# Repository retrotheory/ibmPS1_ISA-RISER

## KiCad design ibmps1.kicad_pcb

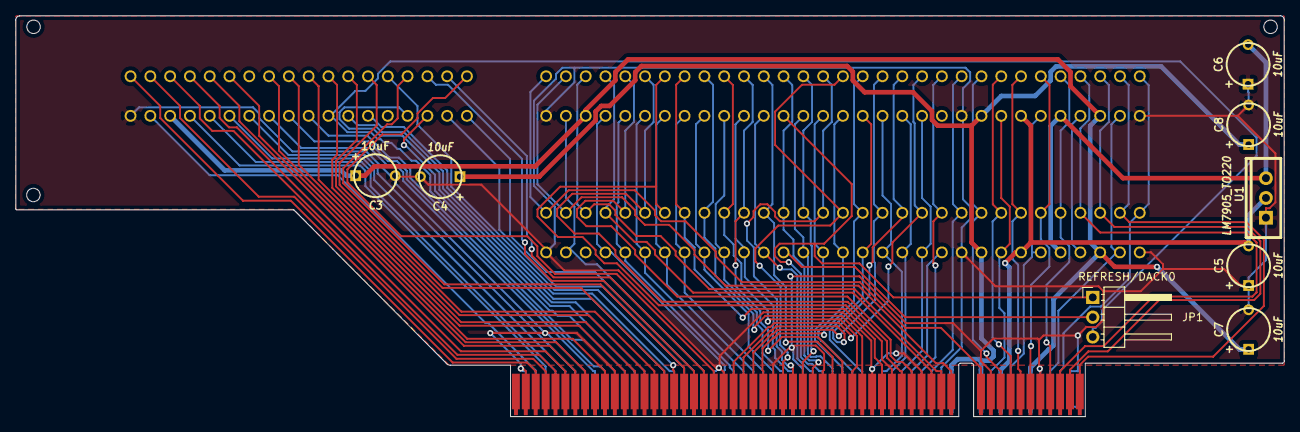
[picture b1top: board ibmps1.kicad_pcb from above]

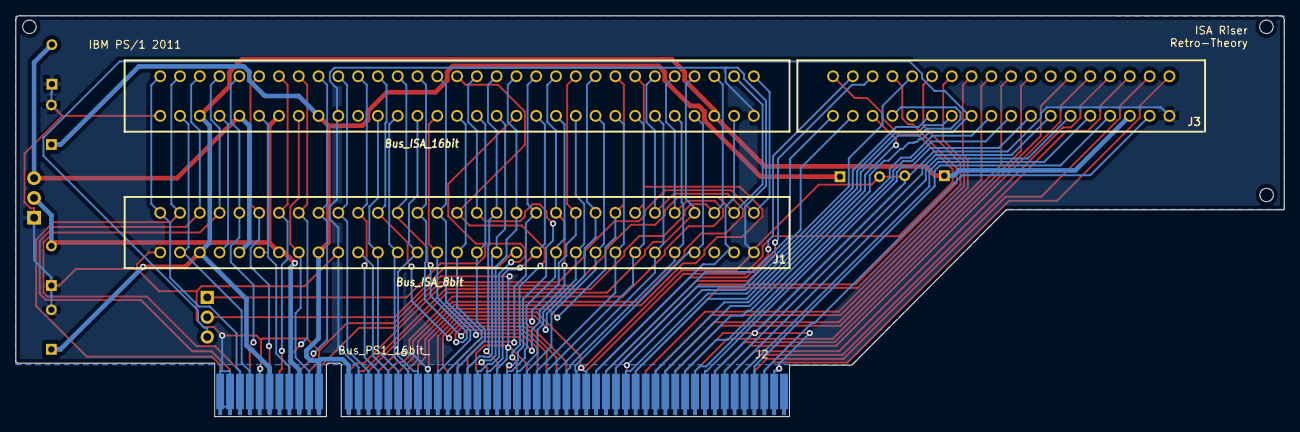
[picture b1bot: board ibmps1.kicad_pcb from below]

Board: 2 copper layers, 162.8 x 51.5 mm, 11 parts (2 on the bottom side), 92 nets.

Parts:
10uF: C3; Cap_Tant_508
C4, C5, C6, C7, C8: 10uF; Cap_Tant_508
J1: Bus_ISA_8bit; Conn_Edge_ISA8
J2: Bus_PS1_16bit_; IBMPS1_PCItypev2
J3: Bus_ISA_16bit; Conn_Edge_ISA16
JP1: REFRESH/DACK0; Pin_Header_Angled_1x03_Pitch2.54mm
U1: LM7905_TO220; IC_TO220-3_Vert

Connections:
5V: 10uF.1, C7.1, J1.3, J2.A57, J3.3, J3.29, J3.78
12V: C4.1, C8.1, J1.9, J2.A49, J2.A52, J3.9
-5V: C6.2, J1.5, J3.5, U1.3
-12V: C5.2, J1.7, J2.A54, J3.7, U1.2
AEN: J1.42, J2.A46, J3.42
ALE: J1.28, J2.A26, J3.28
BA00: J1.62, J2.B52, J3.62
BA01: J1.61, J2.B49, J3.61
BA02: J1.60, J2.B48, J3.60
BA03: J1.59, J2.B47, J3.59
BA04: J1.58, J2.B45, J3.58
BA05: J1.57, J2.B44, J3.57
BA06: J1.56, J2.B43, J3.56
BA07: J1.55, J2.B42, J3.55
BA08: J1.54, J2.B40, J3.54
BA09: J1.53, J2.B39, J3.53
BA10: J1.52, J2.B38, J3.52
BA11: J1.51, J2.B37, J3.51
BA12: J1.50, J2.B35, J3.50
BA13: J1.49, J2.B34, J3.49
BA14: J1.48, J2.B33, J3.48
BA15: J1.47, J2.B32, J3.47
BA16: J1.46, J2.B30, J3.46
BA17: J1.45, J2.B29, J3.45
BA18: J1.44, J2.B28, J3.44
BA19: J1.43, J2.B27, J3.43
CLK: J1.20, J2.A35, J3.20
D8: J2.B14, J3.91
D10: J2.B12, J3.93
D11: J2.B11, J3.94
D12: J2.B10, J3.95
D13: J2.B9, J3.96
D14: J2.B8, J3.97
D15: J2.B7, J3.98
DACK0: J2.A16, J3.70, JP1.3
DACK1: J1.17, J2.A38, J3.17
DACK2: J1.26, J2.A28, J3.26
DACK3: J1.15, J2.A40, J3.15
DACK5: J2.A14, J3.72
DACK6: J2.A11, J3.74
DACK7: J2.A9, J3.76
DB0: J1.40, J2.B54, J3.40
DB1: J1.39, J2.B55, J3.39
DB2: J1.38, J2.B56, J3.38
DB3: J1.37, J2.B57, J3.37
DB4: J1.36, J2.B59, J3.36
DB5: J1.35, J2.B60, J3.35
DB6: J1.34, J2.B61, J3.34
DB7: J1.33, J2.B62, J3.33
DRQ0: J2.A15, J3.71
DRQ1: J1.18, J2.A37, J3.18
DRQ2: J1.6, J2.A55, J3.6
DRQ3: J1.16, J2.A39, J3.16
DRQ5: J2.A13, J3.73
DRQ6: J2.A10, J3.75
DRQ7: J2.A8, J3.77
GND: 10uF.2, C4.2, C5.1, C6.1, C7.2, C8.2, J1.1, J1.10, J1.31, J2.A6, J2.A12, J2.A25, J2.A34, J2.A41, J2.A48, J2.A58, J2.A61, J2.A62, J2.B6, J2.B15, J2.B26, J2.B31, J2.B36, J2.B41, J2.B46, J2.B53, J2.B58, J3.1, J3.10, J3.31, J3.80, U1.1
IO: J1.32, J2.A60, J3.32
IOCS16: J2.A22, J3.64
IOR: J1.14, J2.A42, J3.14
IOW: J1.13, J2.A43, J3.13
IO_READY: J1.41, J2.A47, J3.41
IRQ2: J1.4, J3.4
IRQ3: J1.25, J2.A29, J3.25
IRQ4: J1.24, J2.A30, J3.24
IRQ5: J1.23, J2.A31, J3.23
IRQ6: J1.22, J2.A32, J3.22
IRQ7: J1.21, J2.A33, J3.21
IRQ10: J2.A17, J3.65
IRQ11: J2.A18, J3.66
IRQ14: J2.A20, J3.69
IRQ15: J2.A21, J3.68
LA17: J2.B18, J3.88
LA18: J2.B19, J3.87
LA19: J2.B20, J3.86
LA20: J2.B21, J3.85
LA21: J2.B22, J3.84
LA22: J2.B23, J3.83
LA23: J2.B24, J3.82
MASTER: J2.A7, J3.79
MEMCS16: J2.A23, J3.63
MEMR: J2.B17, J3.89
MEMW: J2.B16, J3.90
OSC: J1.30, J2.A24, J3.30
OWS: J1.8, J2.A53, J3.8
REFRESH: J2.A36, J3.19, JP1.1
RESET: J1.2, J2.A59, J3.2
SBHE: J2.B25, J3.81
SLOTDACK0: J1.19, JP1.2
SMEMR: J1.12, J2.A44, J3.12
SMEMW: J1.11, J2.A45
TC: J1.27, J2.A27, J3.27
